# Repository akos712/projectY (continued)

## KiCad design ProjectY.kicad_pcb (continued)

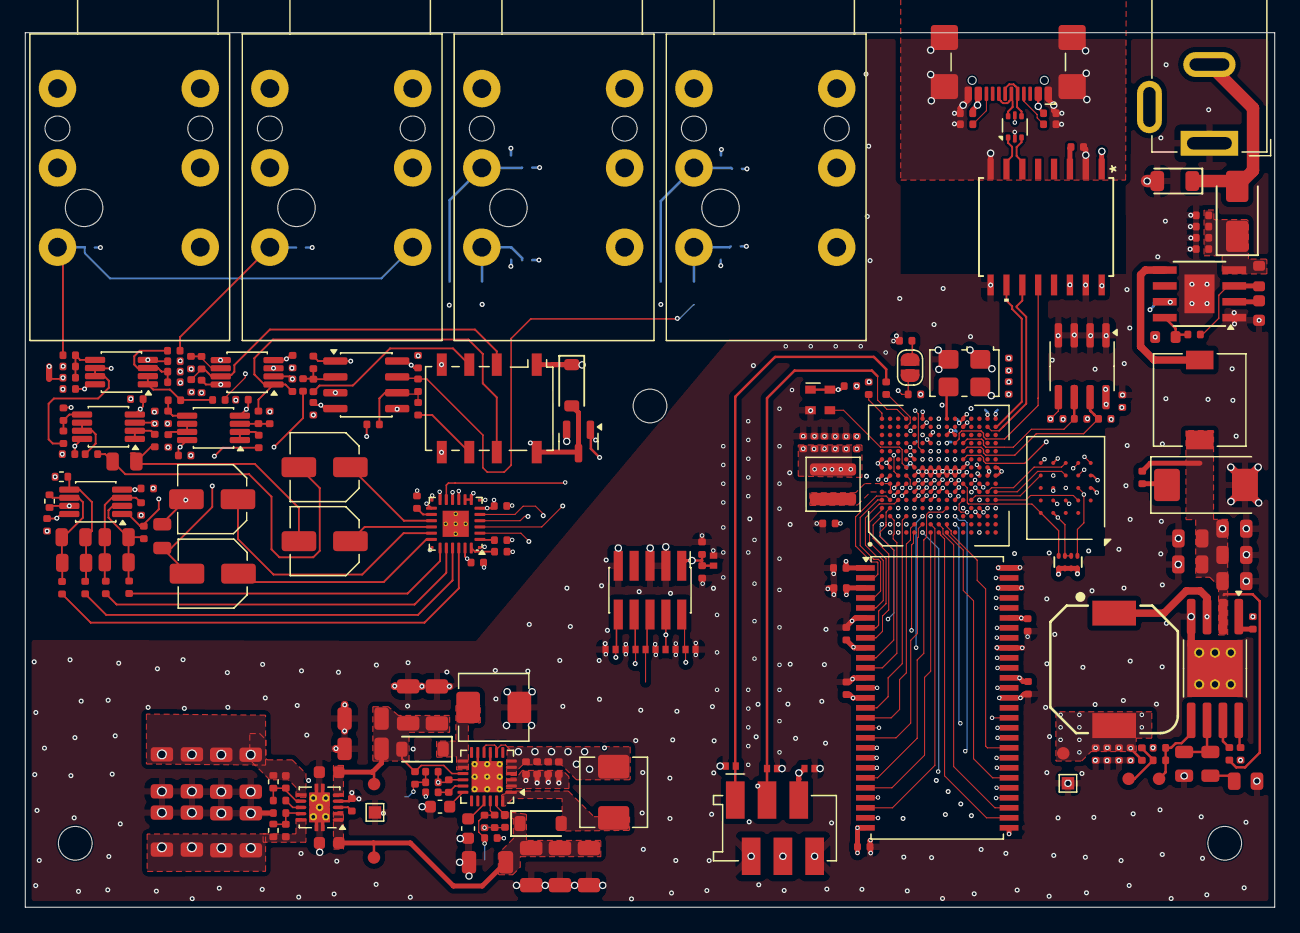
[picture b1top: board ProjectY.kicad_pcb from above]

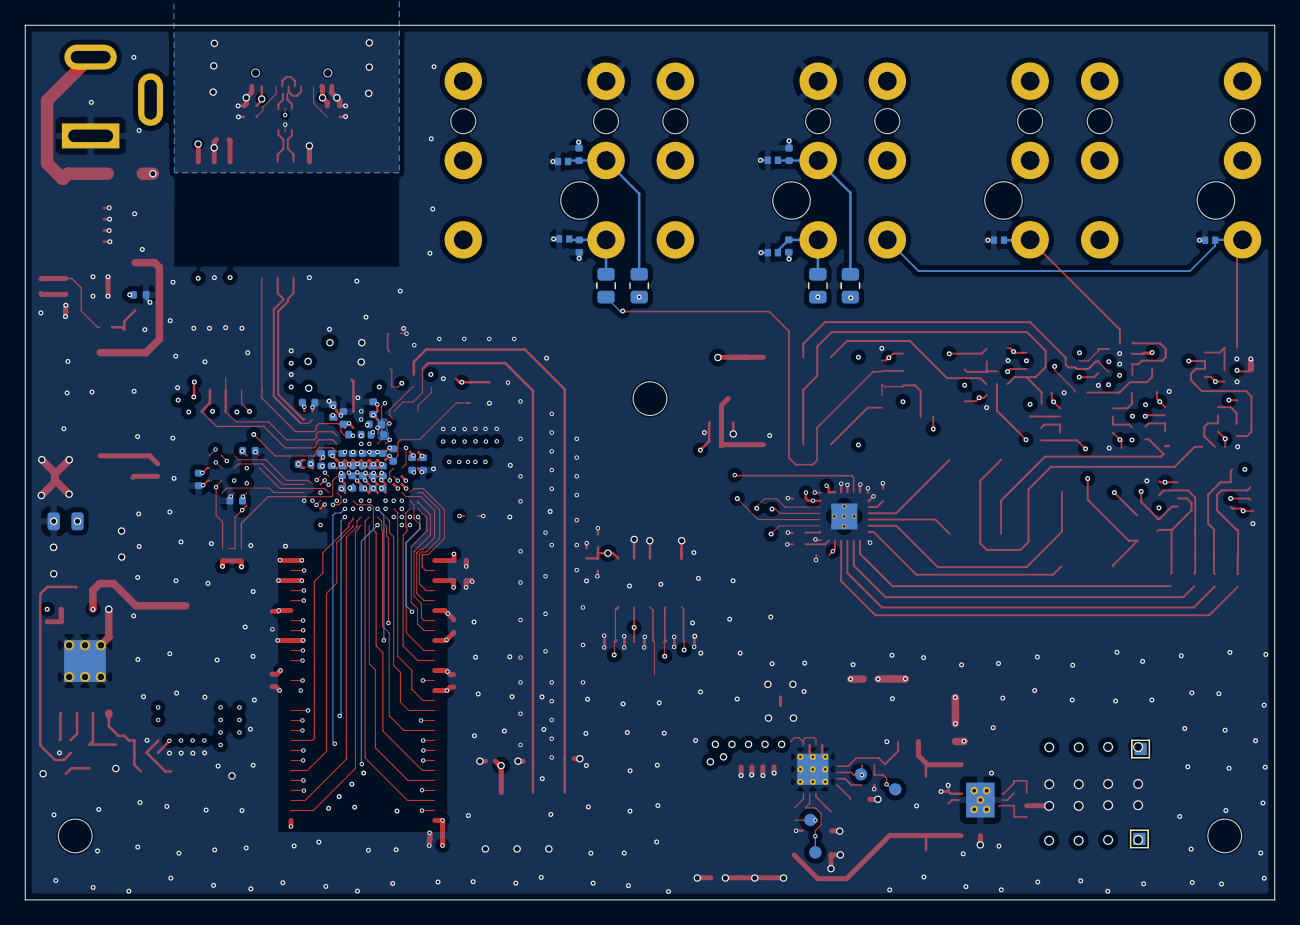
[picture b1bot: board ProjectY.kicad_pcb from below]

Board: 6 copper layers, 100.0 x 70.0 mm, 272 parts (48 on the bottom side), 175 nets.

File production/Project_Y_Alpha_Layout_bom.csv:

Designator,Footprint,Quantity,Value,LCSC Part #
"C10, C11, C112, C113, C114, C115, C116, C117, C118, C119, C120, C24, C35, C36, C37, C39, C40, C41, C42, C43, C45, C47, C5, C6, C60, C61, C62, C64, C65, C67, C68, C7, C70, C72, C73, C74, C75, C76, C77, C78, C80, C90, C91",C_0402,43,4.7uF,C23733
"C106, C107",C_0402,2,6.8pF,C1576
"C108, C109, C110, C111, C131, C156, C157, C158, C32, C33, C34, C51, C55, C94, C95, C96",C_1206,16,47uF,C96123
"C14, C15, C16, C230, C239, C401, C59, C88",C_0402,8,1uF,C52923
"C17, C18, C203, C204, C234, C237, C238, C240",C_0805,8,2.2nF,C28260
"C19, C20, C21, C22, C229, C233, C241, C26, C28, C29, C89",C_0402,11,10uF,C15525
"C201, C202, C219, C220, C50, C63",C_0402,6,100pF,C1546
"C205, C206, C207, C208",C_Elec_5x5.8,4,10uF 16V,C1984751
"C209, C210, C211, C212, C213, C214, C215, C216, C217, C218, C4, C56, C57, C87",C_0402,14,100nF,C1525
"C23, C48, C49, C81, C82, C83",C_0805,6,10uF,C440198
"C3, C54, C84, C85, C86",C_0402,5,100nF,C307331
C31,C_0402,1,220nF,C16772
"C404, C405",C_0603,2,10uF,C96446
C52,CP_EIA-7343-31_Kemet-D,1,"100u, 60mR",
C53,C_0603,1,1uF,C15849
"C66, C79",C_0402,2,10nF,C15195
C97,0603,1,10nF,
C98,0603,1,4.7nF,
D1,D_SOD-123FL,1,SMF20CA,C42371747
"D10, D2, D3, D5, D8, D9",D_DFN1006-2L,6,ESD401,C7420372
"D11, D12, D13, D14, D15, D16, D17, D18, D19",D_DFN1006-2L,9,H5VL10B,C7420372
D20,D_SOD-123,1,1N4148W,C81598
"D4, D7",D_SOD-123,2,B5819W,C64885
D6,D_SMA,1,SS14,C2480
IC2,BGA-225_15x15_11.0x11.0mm,1,R7KA8P1KFLCAB#UC0,
J1,J_Wurth_WR-MM_690367280676,1,UI Board Connector,
"J17, J7",Jack_6.35mm_Neutrik_NRJ6HF_Horizontal,2,Out,
J2,PinHeader_2x05_P1.27mm_Vertical_SMD,1,Conn_ARM_JTAG_SWD_10,
J3,BarrelJack_GCT_DCJ200-10-A_Horizontal,1,9V,
J5,Jack_6.35mm_Neutrik_NRJ6HF_Horizontal,1,IN_R,
J6,Jack_6.35mm_Neutrik_NRJ6HF_Horizontal,1,IN_L,
J9,USB_C_Receptacle_GCT_USB4110,1,USB_C_Receptacle_USB2.0_14P,
K1,Relay_DPDT_Omron_G6K-2F-Y,1,G6K-2,
L1,L_Wuerth_MAPI-4030,1,4.7uH,
L3,WE-PD_1030P,1,4.7uf,
L4,L_7.3x7.3_H3.5,1,22uH,
"L6, L7",L_Sunlord_MWSA0518S,2,10u,C139506
Q3,SOT-23,1,BC846,
"R1, R15",R_0402,2,5.1kΩ,C25905
R11,R_0805,1,22kΩ,C17560
R12,R_0402,1,1,
"R13, R14, R16, R221, R222, R224, R225",R_0402,7,1kΩ,C11702
"R17, R205, R208, R211, R212, R22, R32, R33, R7, R9",R_0402,10,3.3kΩ,C25890
"R18, R26, R28",R_0402,3,100kΩ,C25741
"R2, R23, R25, R29",R_0402,4,47Ω,C25118
"R201, R202, R217, R218, R219, R220",R_0402,6,100Ω,C25076
"R203, R204",R_0402,2,1MΩ,C26083
"R206, R209, R213, R215",R_0402,4,3k,
"R207, R210, R214, R216",R_0402,4,1.3k,
"R223, R227",0402,2,1.65k,
"R226, R228",R_0402,2,1.65k,
"R27, R48",R_0402,2,510kΩ,C11616
"R31, R35, R58, R60",R_0402,4,10kΩ,C25744
"R34, R47",R_0402,2,1.5kΩ,C25867
"R36, R39, R40, R43",0805,4,"100,0.1%",
R44,R_0402,1,12kΩ,C25752
R45,R_0603,1,110kΩ,C25805
R46,R_0603,1,8.2kΩ,C25981
R5,R_0402,1,75kΩ,C25798
R55,R_0402x4,1,10kΩ,C25725
"R59, R61",0402,2,R,
R8,R_0402,1,24kΩ,C25769
TP1,GEN_TP_PCB,1,3.3V,
TP10,GEN_TP_PCB,1,FB3,
TP11,TestPoint_Pad_1.0x1.0mm,1,+6.5V,
TP12,TestPoint_Pad_1.0x1.0mm,1,-6.5V,
TP2,GEN_TP_PCB,1,Bode,
TP3,GEN_TP_PCB,1,FB,
TP4,TestPoint_Pad_1.0x1.0mm,1,3.3V_GND,
TP5,GEN_TP_PCB,1,Bode2,
TP6,GEN_TP_PCB,1,Bode3,
TP7,GEN_TP_PCB,1,7V,
TP8,GEN_TP_PCB,1,-7V,
TP9,GEN_TP_PCB,1,FB2,
U1,TSOP-II-54_22.2x10.16mm_P0.8mm,1,W9825G6KH-6,C97572
U10,SOIC16_DW_TEX-L,1,ISOUSB111DWXR,
U11,SOP-8-1EP_4.57x4.57mm_P1.27mm_EP4.57x4.45mm_ThermalVias,1,RT8293B,
U12,SOT-666,1,USBLC6-2P6,
U13,TI_SO-PowerPAD-8,1,TPS259630,
U17,VQFN-24-1EP_4x4mm_P0.5mm_EP2.5x2.5mm_ThermalVias,1,TPS65131RGET,
U2,BGA-24_6x8mm_Layout5x5_P1.0mm,1,IS25LX512M-JHLE,
"U201, U202, U203, U204, U6",VSSOP-8_3x3mm_P0.65mm,5,OPA1678,
U205,TAC5242,1,TAC5242,
U206,SOIC-8_3.9x4.9mm_P1.27mm,1,OPA1678,
U3,SOIC-8_3.9x4.9mm_P1.27mm,1,FM24CL64B,C9829
U4,Texas_S-PVSON-N10_ThermalVias,1,TPS7A39,C2685819
Y1,Oscillator_SMD_Abracon_ASDMB-4Pin_2.5x2.0mm,1,ASDLJ-E-24.576MHZ-L-R-T,
Y3,Oscillator_SMD_SeikoEpson_SG8002LB-4Pin_5.0x3.2mm,1,SG-5032CAN 24MHz,

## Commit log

2025-07-17 new file: ProjectY.kicad_pcb new file: ProjectY.kicad_prl new file: ProjectY.kicad_pro new file: ProjectY.kicad_sch
2025-07-17 new file: MCU.kicad_sch new file: PSU.kicad_sch modified: ProjectY.kicad_pro modified: ProjectY.kicad_sch new file: ad.kicad_sch new file: audio.kicad_sch new file: usbfilter.kicad_sch
2025-07-17 modified: MCU.kicad_sch modified: PSU.kicad_sch modified: ProjectY.kicad_pro modified: ProjectY.kicad_sch modified: ad.kicad_sch modified: audio.kicad_sch
2025-07-22 modified: MCU.kicad_sch modified: PSU.kicad_sch modified: ProjectY.kicad_pro modified: ProjectY.kicad_sch modified: audio.kicad_sch modified: fp-info-cache new file: spdif.kicad_sch modified: usbfilt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
2025-08-06 git test
2025-08-06 added decoupling for DSP
2025-08-08 started the layout process
2025-08-10 3v3 dcdc update
2025-08-13 deleted usb powering option because of 4.5V minimum input voltage of DC-DC
2025-08-23 lot of changes
2025-08-29 last stm32h7 version
2025-10-03 imrt1176 is added
2025-10-27 added renesas RA8P1
2025-11-14 progressed with SDRAM layout
2025-12-16 layout progress
2026-01-10 progressed with the layout
2026-01-16 DCDC upgraded
2026-01-16 layout is almost finished
2026-01-19 0 airwires finally
2026-01-24 RAM routing was fixed
2026-02-17 signal integrity related fixes
